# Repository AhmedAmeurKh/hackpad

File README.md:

# hackpad
hackpad for hackclub blueprint i made in 18 hours
# CAD:
here's what it looks like:

i made it in fusion 360 about a month ago
# pcb:

this is what i came up with i hope it works
# firmware:
i used QMK's firmware, this proved to be the most confusing hardest part of the project in my opinion thats why i left it on hold for a long time but i managed to figure it out eventually
# BOM:
4x DSA Keycaps
1x XIAO RP2040
1x Case (2 3d printed parts)
4x Cherry MX Switches(or any switch as long as it works)
4x screws (optional)

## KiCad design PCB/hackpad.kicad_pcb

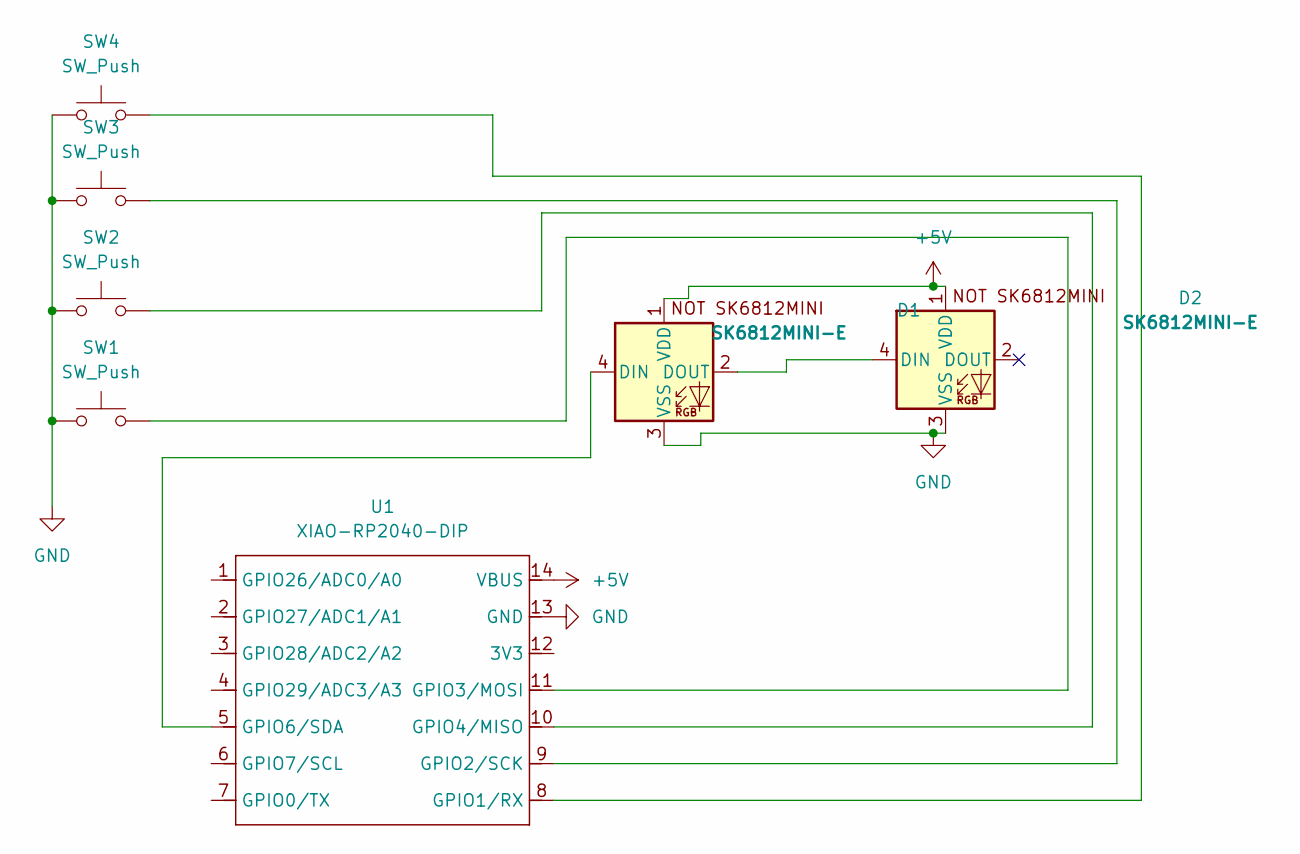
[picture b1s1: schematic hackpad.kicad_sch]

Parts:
D1, D2: SK6812MINI-E; SK6812MINI-E_fixed
SW1, SW2, SW3, SW4: SW_Push; SW_Cherry_MX_1.00u_PCB
U1: XIAO-RP2040-DIP

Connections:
+5V: D1.1 (VDD), D2.1 (VDD), U1.14 (VBUS)
GND: D1.3 (VSS), D2.3 (VSS), SW1.1, SW2.1, SW3.1, SW4.1, U1.13 (GND)
unnamed: D1.4 (DIN), U1.5 (GPIO6/SDA)
unnamed: D1.2 (DOUT), D2.4 (DIN)
unnamed: SW4.2, U1.8 (GPIO1/RX)
unnamed: SW3.2, U1.9 (GPIO2/SCK)
unnamed: SW1.2, U1.11 (GPIO3/MOSI)
unnamed: SW2.2, U1.10 (GPIO4/MISO)

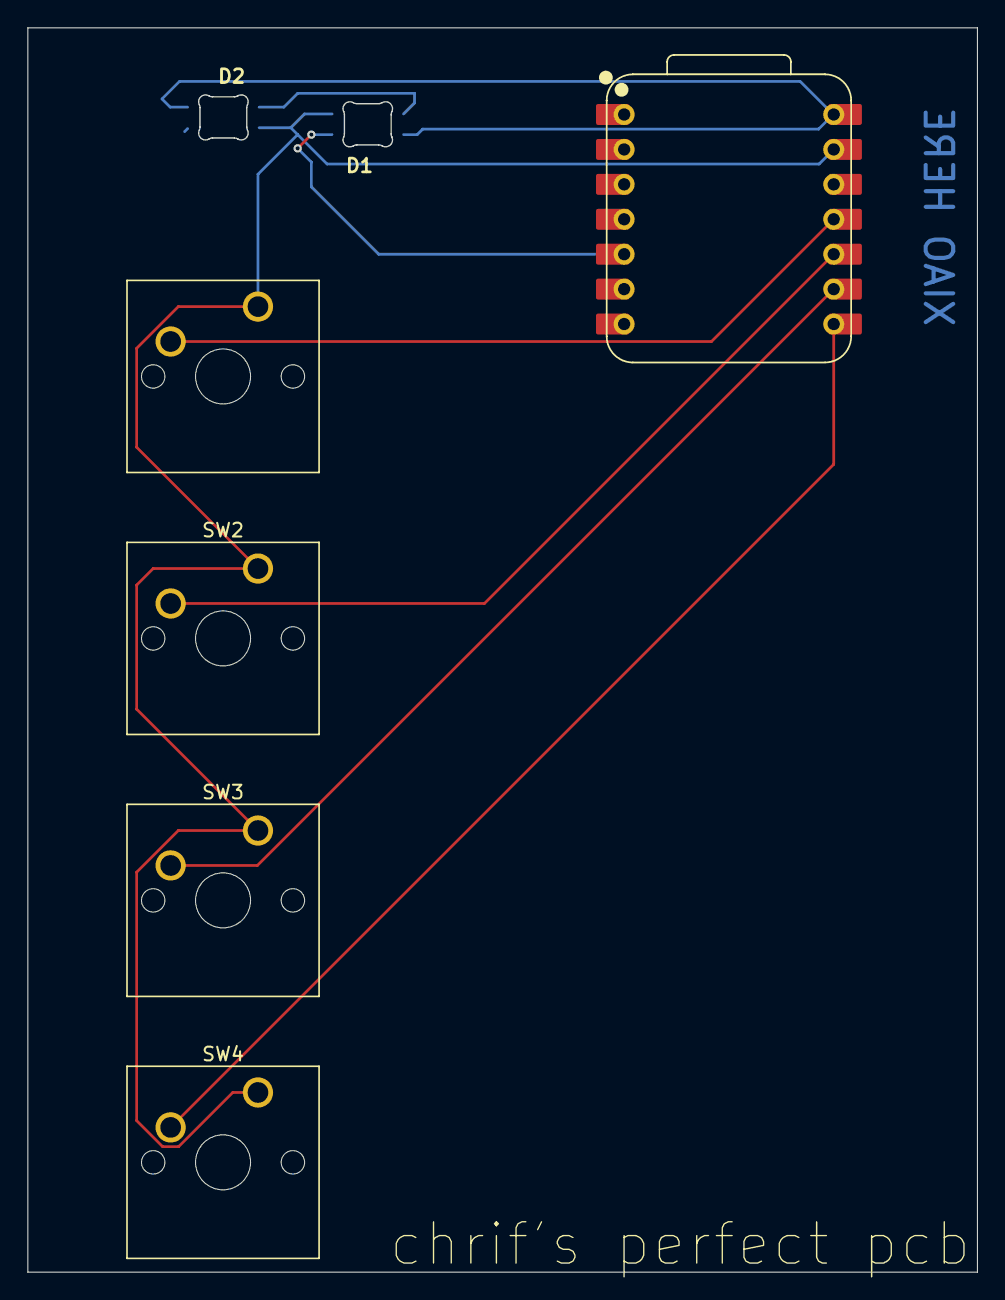
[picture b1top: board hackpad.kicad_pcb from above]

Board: 2 copper layers, 69.1 x 90.5 mm, 7 parts (0 on the bottom side), 8 nets.

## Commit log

2026-03-31 Expand README with project details and images
    Added detailed sections about CAD, PCB, firmware, and BOM.
2026-04-04 Update project duration from 17 to 18 hours
